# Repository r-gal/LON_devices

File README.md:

This repository contains source code and PCB for Home Automation peripheral modules.
Code is in Atmel Studio 7.0 format and it is ready to compile and write to Attiny uC.
Important:
1. Fuse bits must be set to high speed
2. Each module must fave unique address. To assume that definition "#define ADR0" in module *.h ( for example SW3.h) must be stepped and code must be recompiled for each module.

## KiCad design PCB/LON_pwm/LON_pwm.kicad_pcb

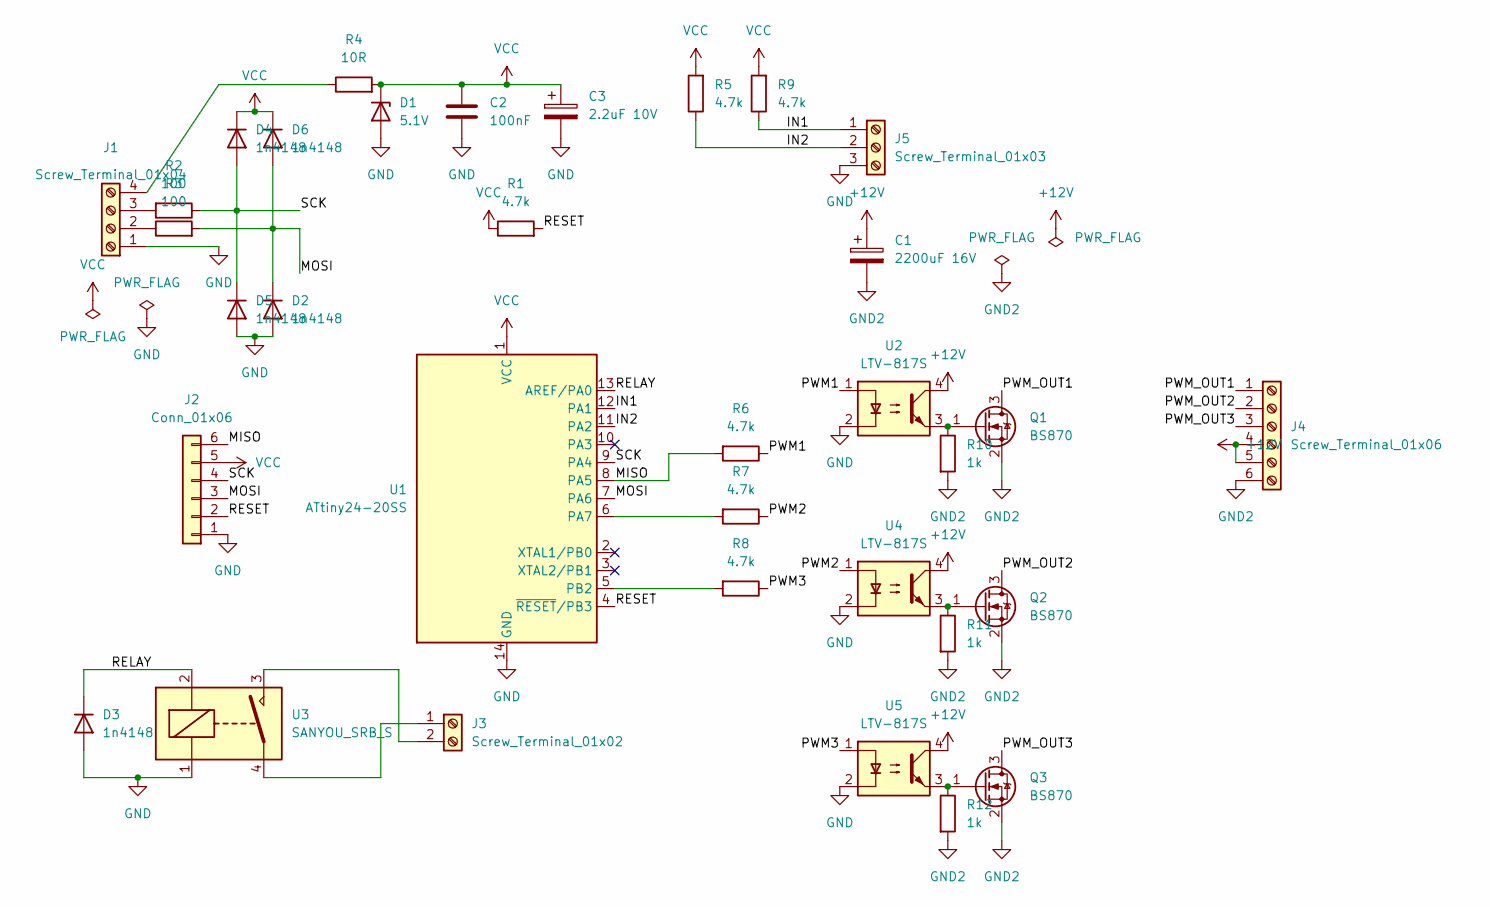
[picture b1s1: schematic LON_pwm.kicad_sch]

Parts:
C1: 2200uF 16V; CP_Radial_D10.0mm_P5.00mm
C2: 100nF; C_0603_1608Metric_Pad1.08x0.95mm_HandSolder
C3: 2.2uF 10V; CP_EIA-3216-18_Kemet-A
D1: 5.1V; D_MiniMELF
D2, D3, D4, D5, D6: 1n4148; D_MiniMELF
J1: Screw_Terminal_01x04; TerminalBlock_4Ucon_1x04_P3.50mm_Horizontal
J2: Conn_01x06; PinHeader_1x06_P1.27mm_Vertical
J3: Screw_Terminal_01x02; TerminalBlock_Phoenix_PT-1,5-2-5.0-H_1x02_P5.00mm_Horizontal
J4: Screw_Terminal_01x06; TerminalBlock_Phoenix_PT-1,5-6-5.0-H_1x06_P5.00mm_Horizontal
J5: Screw_Terminal_01x03; TerminalBlock_4Ucon_1x03_P3.50mm_Horizontal
Q1, Q2, Q3: BS870; SOT-23
R1, R5, R6, R7, R8, R9: 4.7k; R_0805_2012Metric_Pad1.20x1.40mm_HandSolder
R2, R3: 100; R_0805_2012Metric_Pad1.20x1.40mm_HandSolder
R4: 10R; R_0805_2012Metric_Pad1.20x1.40mm_HandSolder
R10, R11, R12: 1k; R_0805_2012Metric_Pad1.20x1.40mm_HandSolder
U1: ATtiny24-20SS; SOIC-14_3.9x8.7mm_P1.27mm
U2, U4, U5: LTV-817S; SMDIP-4_W9.53mm
U3: SANYOU_SRB_S; SANYOU_SRB

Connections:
+12V: C1.1, J4.4, J4.5, U2.4, U4.4, U5.4
/IN1: J5.1, R9.1, U1.12 (PA1)
/IN2: J5.2, R5.1, U1.11 (PA2)
/MISO: J2.6, R6.2, U1.8 (PA5)
/MOSI: D2.1 (K), D6.2 (A), J2.3, R3.2, U1.7 (PA6)
/PWM1: R6.1, U2.1
/PWM2: R7.1, U4.1
/PWM3: R8.1, U5.1
/PWM_OUT1: J4.1, Q1.3 (D)
/PWM_OUT2: J4.2, Q2.3 (D)
/PWM_OUT3: J4.3, Q3.3 (D)
/RELAY: D3.1 (K), U1.13 (AREF/PA0), U3.2
/RESET: J2.2, R1.2, U1.4 (~RESET/PB3)
/SCK: D4.2 (A), D5.1 (K), J2.4, R2.1, U1.9 (PA4)
GND: C2.2, C3.2, D1.2 (A), D2.2 (A), D3.2 (A), D5.2 (A), J1.1, J2.1, J5.3, U1.14 (GND), U2.2, U3.1, U4.2, U5.2
GND2: C1.2, J4.6, Q1.2 (S), Q2.2 (S), Q3.2 (S), R10.2, R11.2, R12.2
unnamed: J1.2, R3.1
unnamed: J1.3, R2.2
unnamed: J1.4, R4.1
unnamed: J3.1, U3.4
unnamed: Q1.1 (G), R10.1, U2.3
unnamed: Q2.1 (G), R11.1, U4.3
unnamed: Q3.1 (G), R12.1, U5.3
unnamed: R7.2, U1.6 (PA7)
unnamed: R8.2, U1.5 (PB2)
unnamed: J3.2, U3.3
VCC: C2.1, C3.1, D1.1 (K), D4.1 (K), D6.1 (K), J2.5, R1.1, R4.2, R5.2, R9.2, U1.1 (VCC)

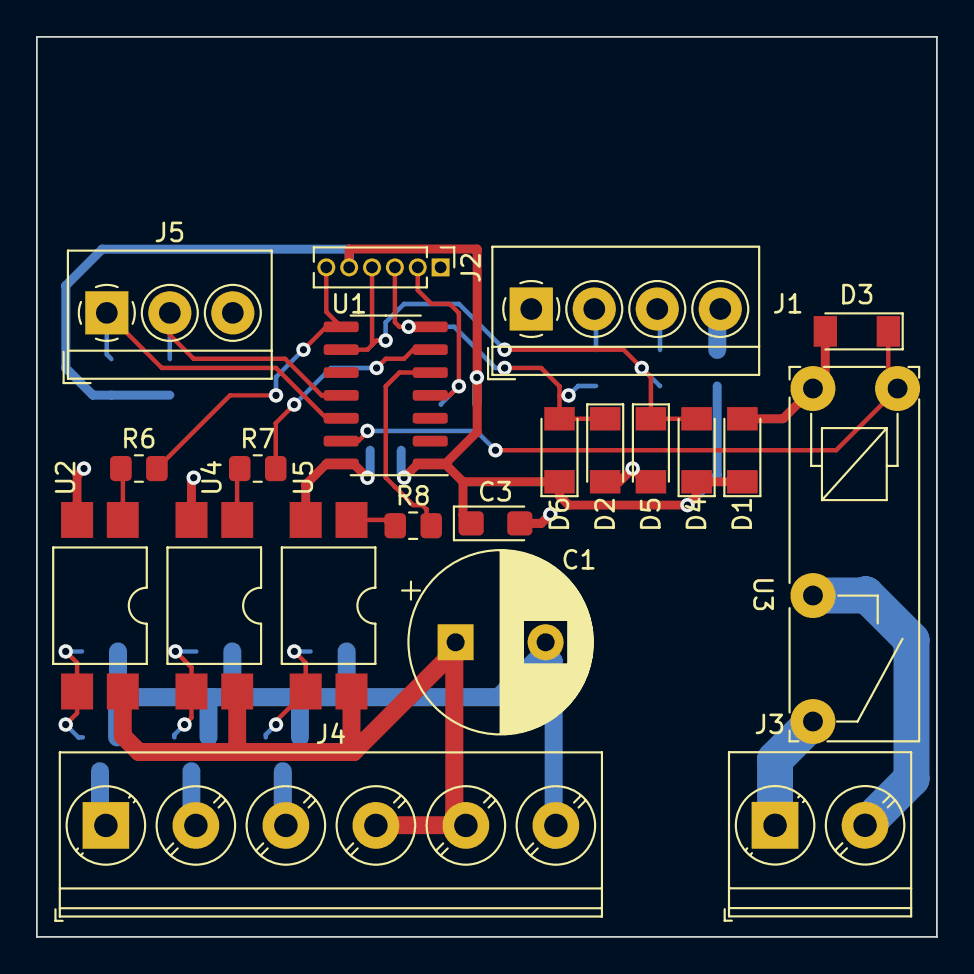
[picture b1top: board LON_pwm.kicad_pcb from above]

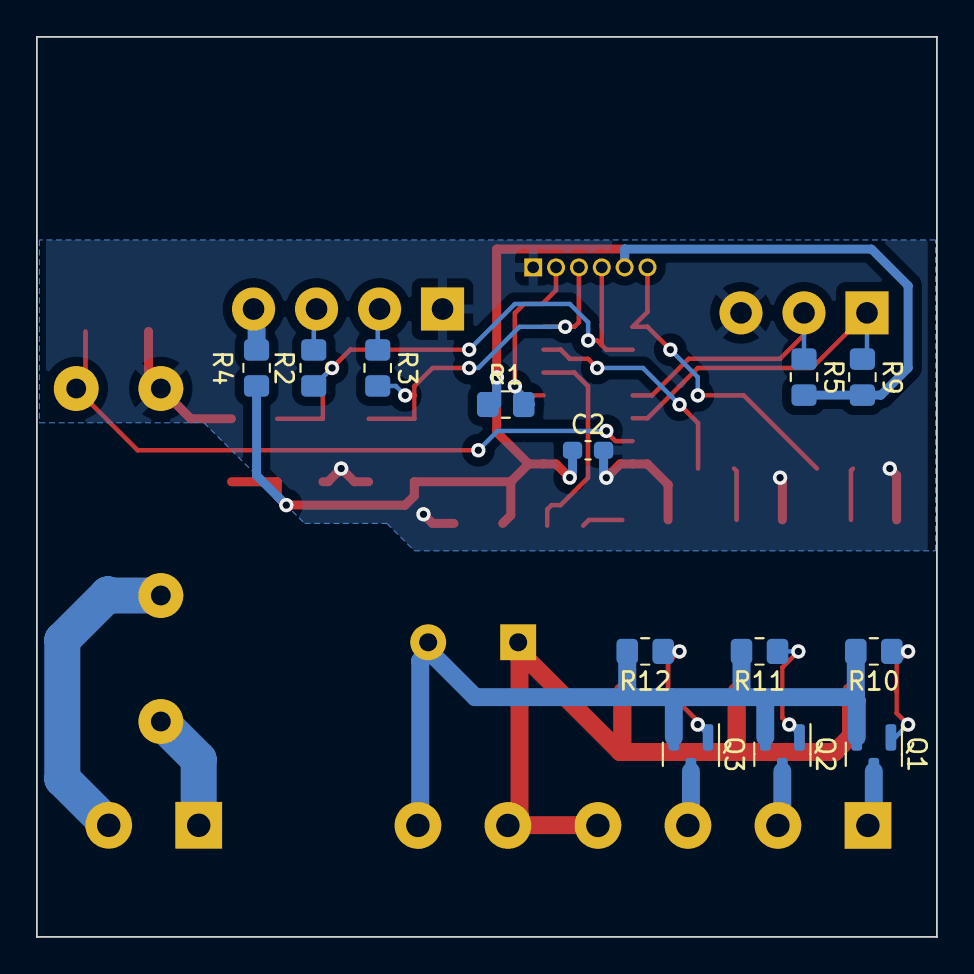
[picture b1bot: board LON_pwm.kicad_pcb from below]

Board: 2 copper layers, 50.0 x 50.0 mm, 34 parts (13 on the bottom side), 27 nets.

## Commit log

2025-07-09 Create LICENSE
